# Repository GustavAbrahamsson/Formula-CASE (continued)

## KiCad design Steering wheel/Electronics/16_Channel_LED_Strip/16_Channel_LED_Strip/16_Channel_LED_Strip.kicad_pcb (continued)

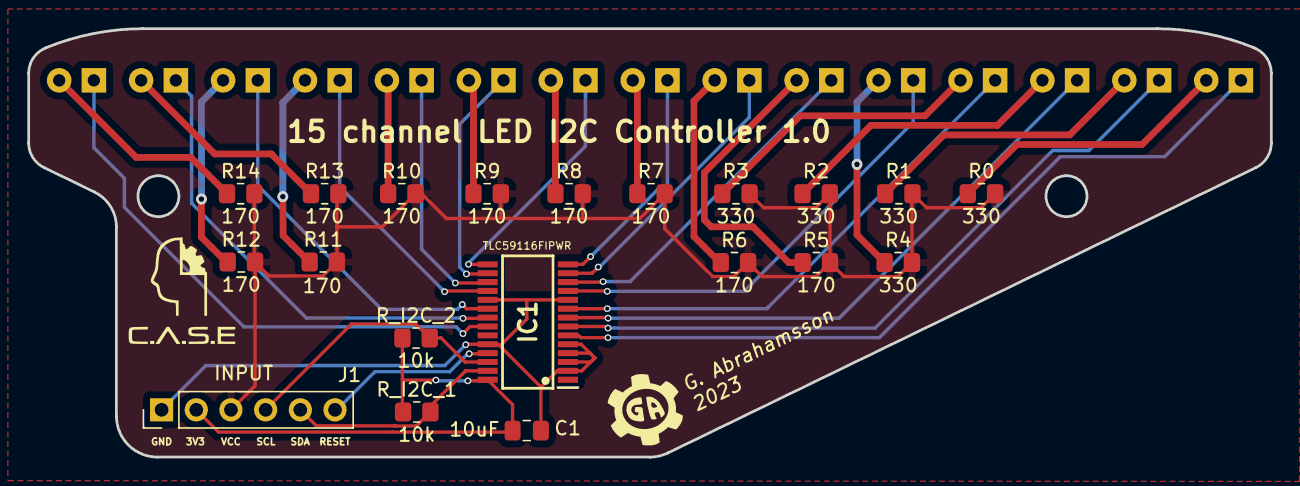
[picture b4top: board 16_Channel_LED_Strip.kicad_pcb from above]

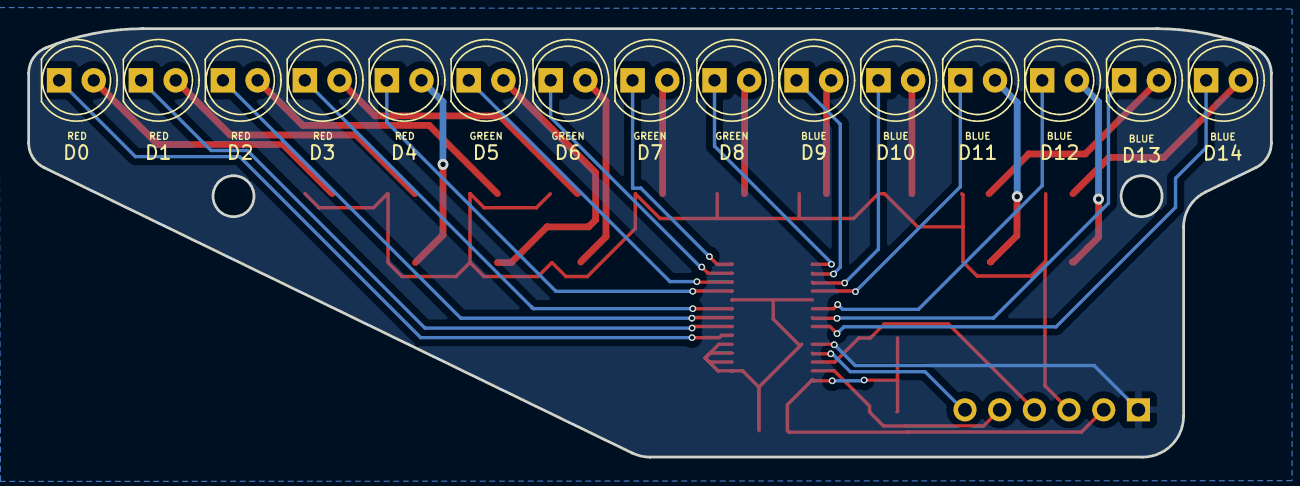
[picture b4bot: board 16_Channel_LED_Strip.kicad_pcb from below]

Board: 2 copper layers, 91.0 x 31.4 mm, 35 parts (15 on the bottom side), 36 nets.

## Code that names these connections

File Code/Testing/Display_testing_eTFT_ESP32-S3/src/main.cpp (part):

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#include "TLC_LED_Array.h"

// Pins
#define BAT_LEVEL_PIN GPIO_NUM_1
#define VOLUME_PIN GPIO_NUM_2

#define BTN1_PIN GPIO_NUM_4
#define BTN2_PIN GPIO_NUM_5
#define BTN3_PIN GPIO_NUM_6
#define BTN4_PIN GPIO_NUM_7

#define L_TRIGGER_PIN GPIO_NUM_17
#define R_TRIGGER_PIN GPIO_NUM_18

#define BUZZ_2_PIN GPIO_NUM_41
#define BUZZ_1_PIN GPIO_NUM_40
#define BZR_1_CHANNEL 0
#define BZR_2_CHANNEL 5

#define L_PADDLE_PIN GPIO_NUM_39
#define R_PADDLE_PIN GPIO_NUM_38

#define ENC_B_PIN GPIO_NUM_48
#define ENC_A_PIN GPIO_NUM_47
#define ENC_SW_PIN GPIO_NUM_21

#define LED_RESET GPIO_NUM_42
#define LED_DRIVER_ADDR 0x60 // ?

// 15-LED array object
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}

void setup_pins(){
  #define BAT_LEVEL_PIN GPIO_NUM_1
  #define VOLUME_PIN GPIO_NUM_2

  #define BTN1_PIN GPIO_NUM_4
  #define BTN2_PIN GPIO_NUM_5
  #define BTN3_PIN GPIO_NUM_6
  #define BTN4_PIN GPIO_NUM_7

  #define L_TRIGGER_PIN GPIO_NUM_17
  #define R_TRIGGER_PIN GPIO_NUM_18

  #define BUZZ_2_PIN GPIO_NUM_41
  #define BUZZ_1_PIN GPIO_NUM_40

  #define L_PADDLE_PIN GPIO_NUM_39
  #define R_PADDLE_PIN GPIO_NUM_38

  pinMode(BAT_LEVEL_PIN, INPUT);
  pinMode(VOLUME_PIN, INPUT);

  pinMode(BTN1_PIN, INPUT_PULLDOWN);
  pinMode(BTN2_PIN, INPUT_PULLDOWN);
  pinMode(BTN3_PIN, INPUT_PULLDOWN);
  pinMode(BTN4_PIN, INPUT_PULLDOWN);
  
  pinMode(L_TRIGGER_PIN, INPUT);
  pinMode(R_TRIGGER_PIN, INPUT);

  ledcAttachPin(BUZZ_1_PIN, BZR_1_CHANNEL);
  ledcAttachPin(BUZZ_2_PIN, BZR_2_CHANNEL);
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
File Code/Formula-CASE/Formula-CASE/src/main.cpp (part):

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#define HALL_EFF_3_PIN 7

// Buzzer
#define BUZZER_PIN 2

// Battery measurement
#define BAT_SENSE_PIN 21

// Motor direction pins
#define M0_DIR_PIN 10
#define M1_DIR_PIN 11
#define M2_DIR_PIN 12
#define M3_DIR_PIN 13

// Servo pins
#define SERVO_PIN 1

#define SERVO_DEFLECTION 50 // deg

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#define BUZZER_CHNL 7

// Motor sense pins ADC
#define M0_SENSE_PIN 15 // 0
#define M1_SENSE_PIN 16
#define M2_SENSE_PIN 17
#define M3_SENSE_PIN 18

#define MOTOR_PWM_BIT_RES 8
#define MOTOR_PWM_FREQ 25000
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
    wheel_throttle *= torque_map(m_meas[0].w_m, current_gear, 2, 5, 10, 15, 1);

    servo.write(int(90 - constrain(wheel_angle * 50.0/90.0, -50.0, 50.0)));
  
    if(wheel_throttle > 0){
      // Temp
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  digitalWrite(M3_REV_PIN, 0);

  // Motor directions
  pinMode(M0_DIR_PIN, OUTPUT);
  pinMode(M1_DIR_PIN, OUTPUT);
  pinMode(M2_DIR_PIN, OUTPUT);
  pinMode(M3_DIR_PIN, OUTPUT);

  digitalWrite(M0_DIR_PIN, 1);
  digitalWrite(M1_DIR_PIN, 0);
  digitalWrite(M2_DIR_PIN, 0);
  digitalWrite(M3_DIR_PIN, 0);

  // Buzzer
  ledcAttachPin(BUZZER_PIN, BUZZER_CHNL);
}

void init_motors(){
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  Serial.println("Car started");

  servo.setPeriodHertz(50);
	servo_channel = servo.attach(SERVO_PIN, 925, 1925);
  servo.write(90);

  init_pins();
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
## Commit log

2022-12-17 Init Matlab
2022-12-18 Calculations
2023-01-17 Init component research
2023-01-18 Add outrunner tyre prototype STL
2023-01-25 Begin PCB
2023-01-28 Prototype 2
2023-01-29 Begin electric motor control design
2023-03-19 Continue PCB-design
2023-09-02 Restart project
2023-09-22 Add pictures
2023-09-23 Add dash display demo
2023-10-02 Add stl-files
2023-10-04 Add stl
2023-10-06 FC control board V1.0
    As ordered from JLC
2023-10-06 First wireless test
2023-10-06 Moved files
2023-10-06 Added PCB media
2023-10-07 Wheel PCB 1.0
2023-10-07 Finish up wheel PCB
2023-10-07 Polish Wheel PCB [ Ordered ]
2023-10-08 Init LED controller PCB
2023-10-18 Simple analog test, ex. for hall sensor
2023-10-18 Start of code for FC-control-board
2023-10-19 Finish LED PCB [Ordered]
2023-10-22 WIP espnow test with controller
2023-10-22 FC control board v1.1 [Ordered]
2023-11-04 Sync old files
2023-11-04 Sync old files #2
2023-11-04 Add successful TFT-display demo with ESP32-S3
    ESP32-S2 worked fine, S3 took some time. Note 'platformio.ini' with USB flags. New library for the TFT display
2023-11-05 Implement gear shifter demo on S3
2023-11-05 Stable TFT (THT_RST to GPIO fix)
2023-11-06 FC_Wheel_PCB 2.0 [Ordered]
2023-11-07 TLC59116 library from Github compiles
2023-11-07 Implement functional RPM LED array
2023-11-07 Sync
2023-11-10 Init TLC_LED_Array class
2023-11-11 Fancy but buggy 'ramp_set()'
2023-11-11 Implement 'TLC_LED_Array' class
2023-11-23 Add code to PCB 2.0
2023-11-24 Add gear shifting and throttle demo
2023-11-26 Add and fix .gitignore
2023-11-26 Init display library
2023-11-26 Implement stable gear shifting with better structure
2023-11-26 Fix neutral indicator
2023-11-28 Add throttle and braking measurement with basic filters
2023-11-30 Begin IMU class
2023-12-02 Angle from IMU, throttle bar, braking bar
2023-12-06 First Formula-CASE car tested
2023-12-07 Continue PWM debugging
2023-12-09 Begin FC Control Board 1.3
2023-12-10 Continue FC 1.3
2023-12-11 FC 1.3 -> FC 2.0
2023-12-12 Functioning 1.2 prototype
2023-12-20 Add clamping diodes and opto couplers
2024-01-02 Final version of 2.0 [Ordered]
2024-01-18 Working 2.0 code
2024-01-25 Continue coding
2024-01-26 Add decent speed measurement
2024-01-28 Add .stl for v35
2024-02-08 Old testing stuff
2024-03-02 Implement IMU functionality
2024-03-02 Add sensor calibration MATLAB script
2024-03-11 Fix sensor resolution, fix noise statistics
2024-03-24 Hall sensor notes
2024-11-10 Add pictures and GIFs
